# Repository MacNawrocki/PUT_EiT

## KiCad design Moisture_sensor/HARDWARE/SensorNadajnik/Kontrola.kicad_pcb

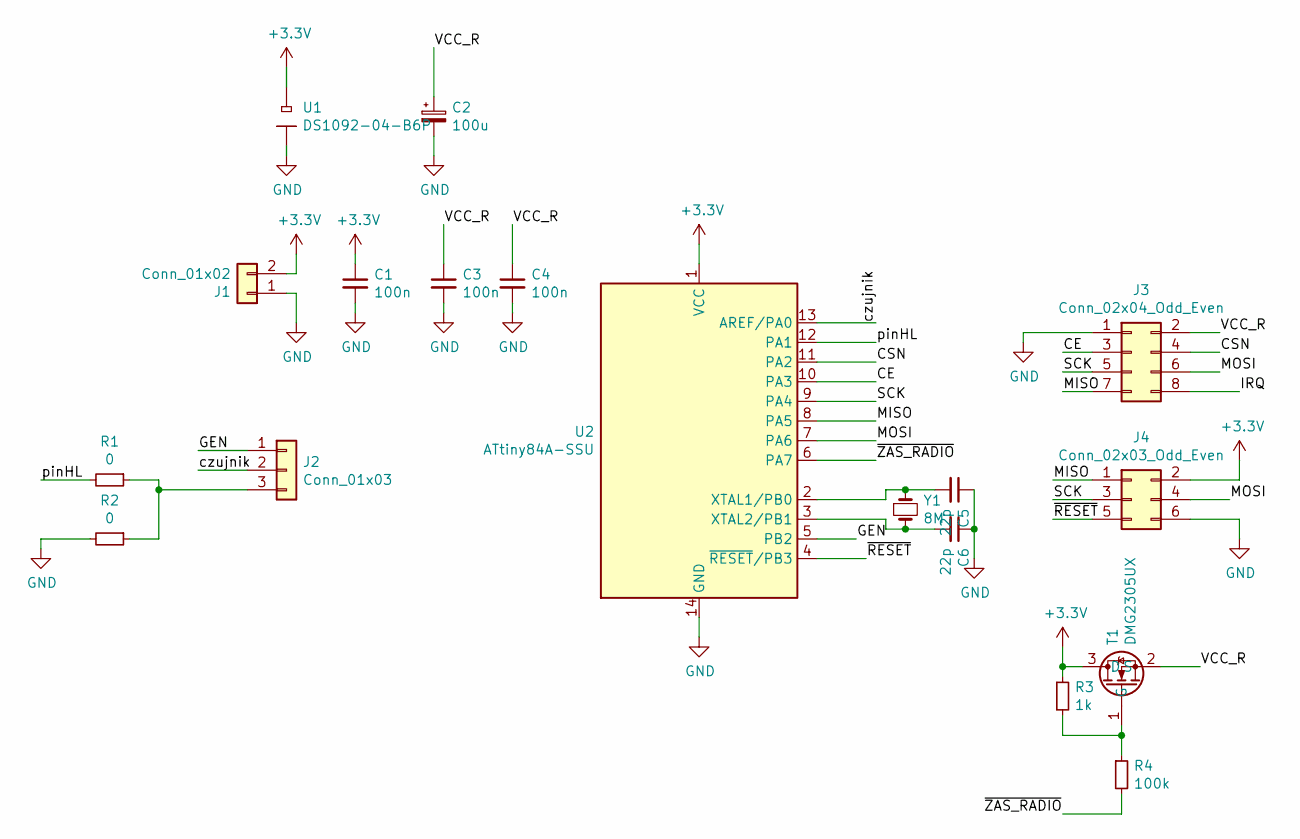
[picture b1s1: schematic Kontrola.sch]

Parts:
C1, C3, C4: 100n; C_0805_2012Metric_Pad1.15x1.40mm_HandSolder
C2: 100u; CP_EIA-3528-21_Kemet-B_Pad1.50x2.35mm_HandSolder
C5, C6: 22p; C_0805_2012Metric_Pad1.15x1.40mm_HandSolder
J1: Conn_01x02; PinHeader_1x02_P2.54mm_Vertical
J2: Conn_01x03; PinHeader_1x03_P2.54mm_Horizontal
J3: Conn_02x04_Odd_Even; PinHeader_2x04_P2.54mm_Vertical
J4: Conn_02x03_Odd_Even; PinHeader_2x03_P2.54mm_Vertical
R1, R2: 0; R_0805_2012Metric_Pad1.15x1.40mm_HandSolder
R3: 1k; R_0805_2012Metric_Pad1.15x1.40mm_HandSolder
R4: 100k; R_0805_2012Metric_Pad1.15x1.40mm_HandSolder
T1: DMG2305UX; SOT23_NASZE
U1: DS1092-04-B6P
U2: ATtiny84A-SSU; SOIC-14_3.9x8.7mm_P1.27mm
Y1: 8M; Crystal_HC49-4H_Vertical

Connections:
+3V3: C1.1, J1.2, J4.2, R3.1, T1.3 (D), U1.2 (-), U2.1 (VCC)
/CE: J3.3, U2.10 (PA3)
/CSN: J3.4, U2.11 (PA2)
/GEN: J2.1, U2.5 (PB2)
/IRQ: J3.8
/MISO: J3.7, J4.1, U2.8 (PA5)
/MOSI: J3.6, J4.4, U2.7 (PA6)
/SCK: J3.5, J4.3, U2.9 (PA4)
/VCC_R: C2.1, C3.1, C4.1, J3.2, T1.2 (S)
/czujnik: J2.2, U2.13 (AREF/PA0)
/pinHL: R1.2, U2.12 (PA1)
/~RESET: J4.5, U2.4 (~RESET~/PB3)
/~ZAS_RADIO: R4.2, U2.6 (PA7)
GND: C1.2, C2.2, C3.2, C4.2, C5.1, C6.1, J1.1, J3.1, J4.6, R2.2, U1.1 (+), U2.14 (GND)
unnamed: C5.2, U2.2 (XTAL1/PB0), Y1.1
unnamed: C6.2, U2.3 (XTAL2/PB1), Y1.2
unnamed: J2.3, R1.1, R2.1
unnamed: R3.2, R4.1, T1.1 (G)

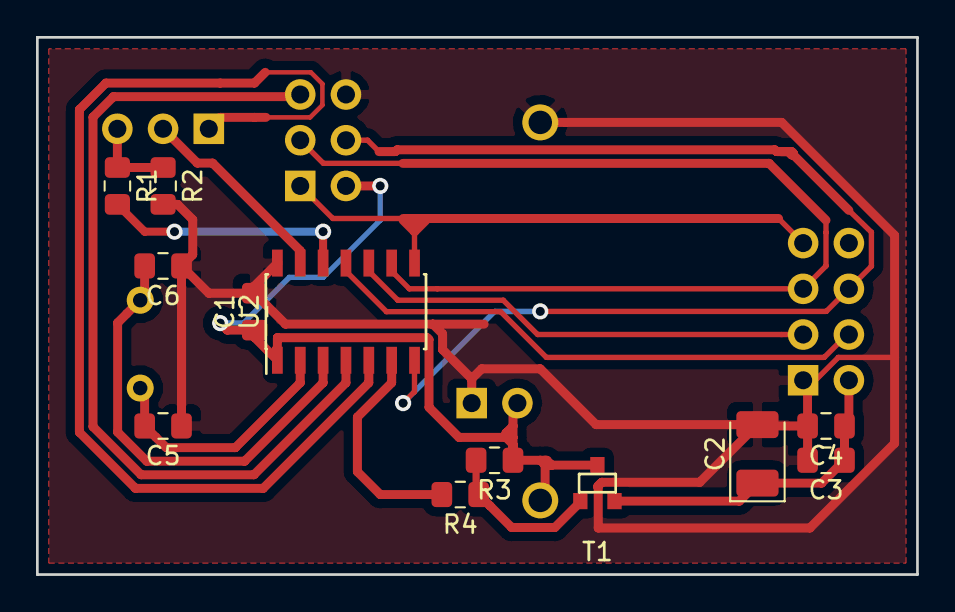
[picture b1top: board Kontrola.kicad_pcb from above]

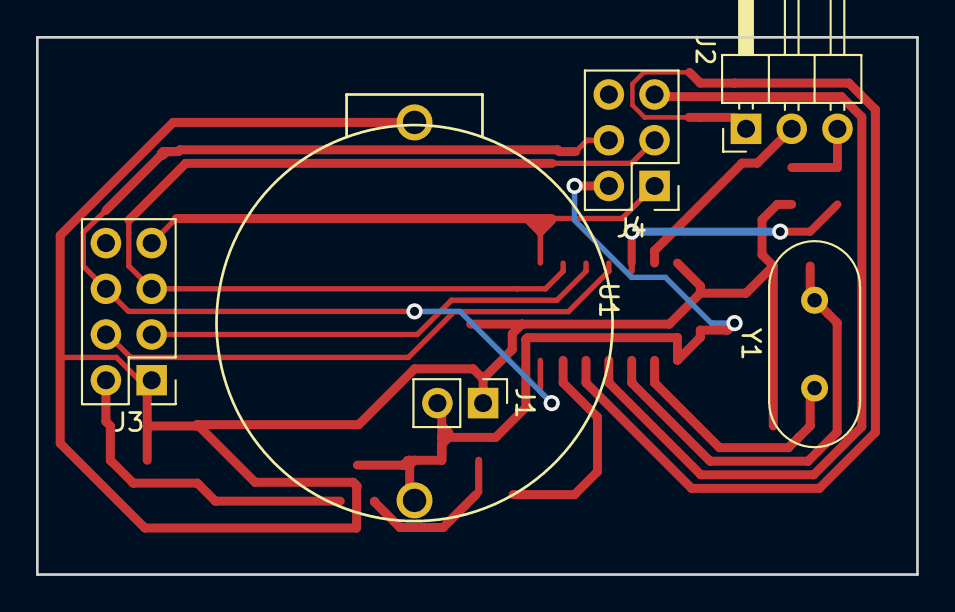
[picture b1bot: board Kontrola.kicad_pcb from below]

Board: 2 copper layers, 48.9 x 29.8 mm, 18 parts (6 on the bottom side), 17 nets.

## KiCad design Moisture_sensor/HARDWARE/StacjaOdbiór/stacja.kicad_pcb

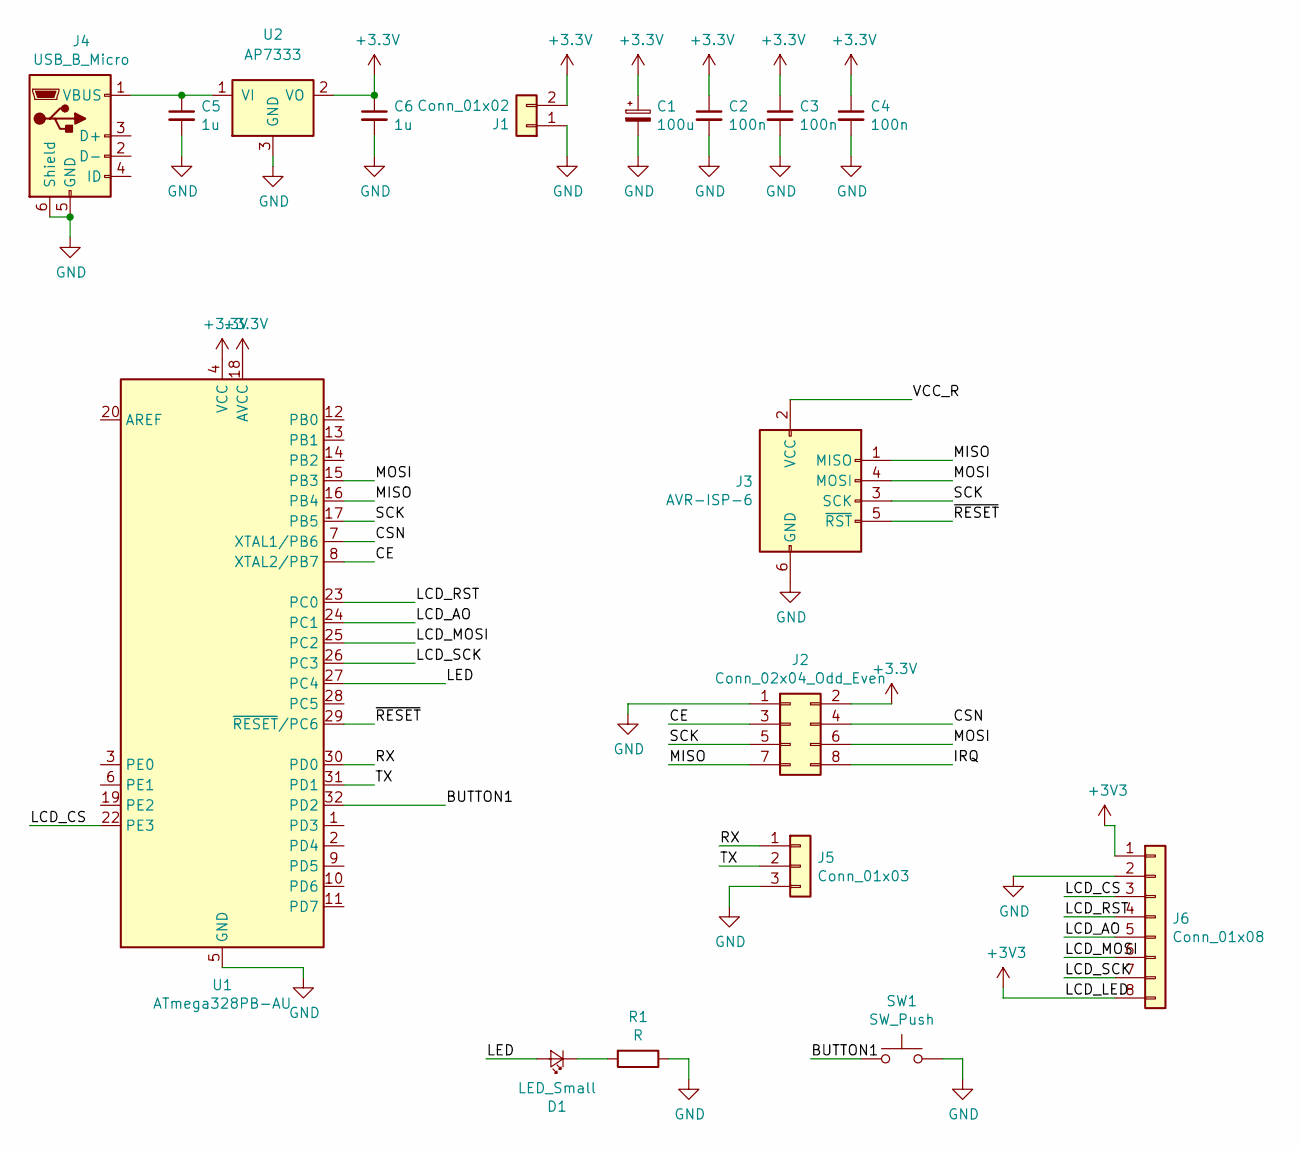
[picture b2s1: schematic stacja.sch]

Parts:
C1: 100u; CP_EIA-3528-21_Kemet-B_Pad1.50x2.35mm_HandSolder
C2, C3, C4: 100n; C_0805_2012Metric_Pad1.15x1.40mm_HandSolder
C5, C6: 1u; C_0805_2012Metric_Pad1.15x1.40mm_HandSolder
D1: LED_Small; LED_0805_2012Metric_Pad1.15x1.40mm_HandSolder
J1: Conn_01x02; PinHeader_1x02_P2.54mm_Vertical
J2: Conn_02x04_Odd_Even; PinHeader_2x04_P2.54mm_Vertical
J3: AVR-ISP-6; PinHeader_2x03_P2.54mm_Vertical
J4: USB_B_Micro; microusb
J5: Conn_01x03; PinHeader_1x03_P2.54mm_Vertical
J6: Conn_01x08; PinHeader_1x08_P2.54mm_Vertical
R1: R; R_0805_2012Metric_Pad1.15x1.40mm_HandSolder
SW1: SW_Push; BUTTON
U1: ATmega328PB-AU; TQFP-32_7x7mm_P0.8mm
U2: AP7333; SOT-23

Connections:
/BUTTON1: SW1.1, U1.32 (PD2)
/CE: J2.3, U1.8 (XTAL2/PB7)
/CSN: J2.4, U1.7 (XTAL1/PB6)
/IRQ: J2.8
/LCD_AO: J6.5, U1.24 (PC1)
/LCD_CS: J6.3, U1.22 (PE3)
/LCD_MOSI: J6.6, U1.25 (PC2)
/LCD_RST: J6.4, U1.23 (PC0)
/LCD_SCK: J6.7, U1.26 (PC3)
/LED: D1.2 (A), U1.27 (PC4)
/MISO: J2.7, J3.1 (MISO), U1.16 (PB4)
/MOSI: J2.6, J3.4 (MOSI), U1.15 (PB3)
/RX: J5.1, U1.30 (PD0)
/SCK: J2.5, J3.3 (SCK), U1.17 (PB5)
/TX: J5.2, U1.31 (PD1)
/VCC_R: J3.2 (VCC)
/~RESET: J3.5 (~RST), U1.29 (~RESET~/PC6)
GND: C1.2, C2.2, C3.2, C4.2, C5.2, C6.2, J1.1, J2.1, J3.6 (GND), J4.5 (GND), J4.6 (Shield), J5.3, J6.2, R1.1, SW1.2, U1.5 (GND), U1.21 (GND), U2.3 (GND)
unnamed: C5.1, J4.1 (VBUS), U2.1 (VI)
unnamed: D1.1 (K), R1.2

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
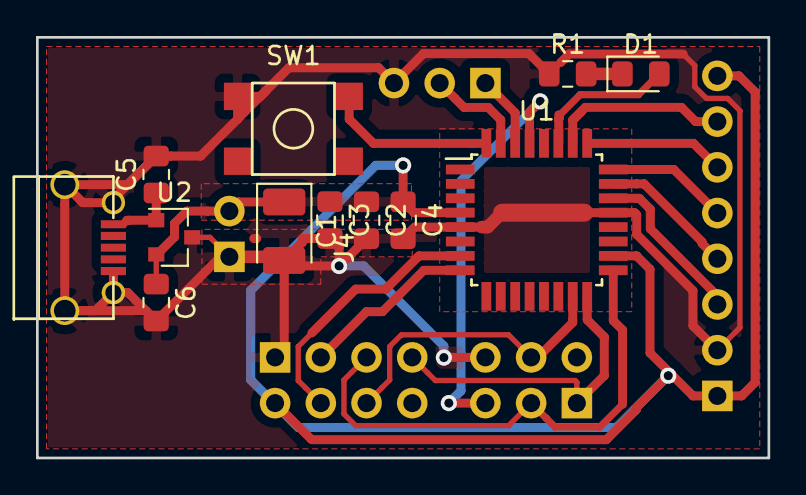
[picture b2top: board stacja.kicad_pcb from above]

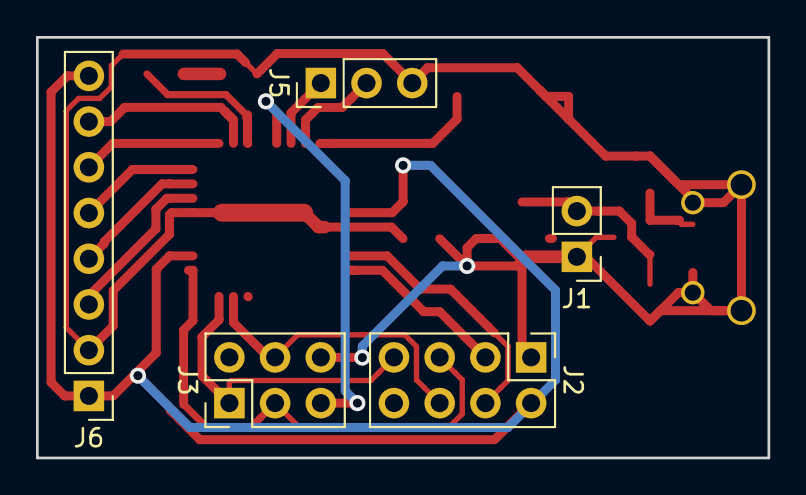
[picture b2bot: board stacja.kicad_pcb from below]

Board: 2 copper layers, 40.6 x 23.4 mm, 17 parts (5 on the bottom side), 19 nets.

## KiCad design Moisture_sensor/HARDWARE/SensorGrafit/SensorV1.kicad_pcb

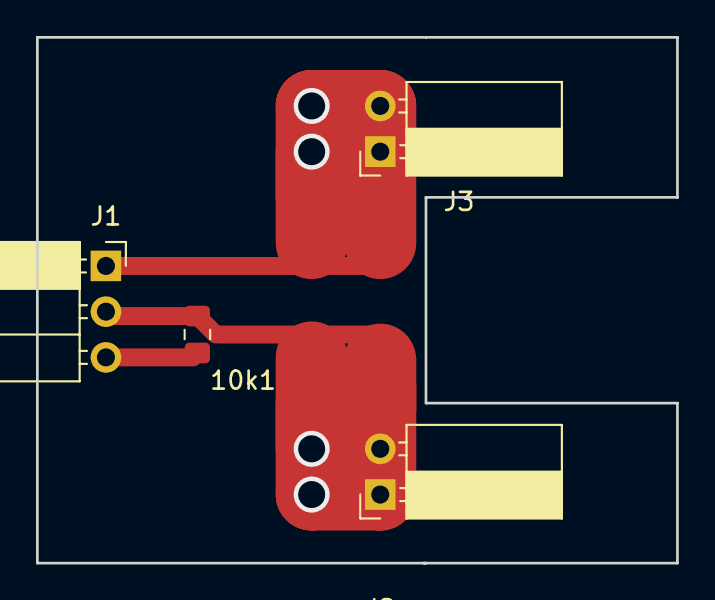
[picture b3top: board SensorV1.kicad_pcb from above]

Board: 2 copper layers, 35.6 x 29.2 mm, 4 parts (0 on the bottom side), 3 nets.

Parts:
10k1: R_Small; R_0805_2012Metric_Pad1.15x1.40mm_HandSolder
J1: Conn_01x03; PinSocket_1x03_P2.54mm_Horizontal
J2, J3: Conn_01x02; PinSocket_1x02_P2.54mm_Horizontal

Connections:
unnamed: 10k1.1, J1.2, J2.1, J2.2
unnamed: 10k1.2, J1.3
unnamed: J1.1, J3.1, J3.2

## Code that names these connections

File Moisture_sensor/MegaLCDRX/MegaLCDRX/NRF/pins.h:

#ifndef PINS_H_
#define PINS_H_

/*
Connection:
ATMega328PB	PIN	To
PB3	to	MOSI		programator/radio
PB4	to	MISO		programator/radio
PB5	to	SCK			programator/radio
PB6	to	CSN			radio
PB7	to	CE			radio
PC0	to	LCD_RST		wywietlacz
PC1	to	LCD_AO		wywietlacz
PC2	to	LCD_MOSI	wywietlacz
PC3	to	LCD_SCK		wywietlacz
PC4	to	LED			dioda na p³ytce
PC6	to	RESET		programator/radio
PD0	to	RX
PD1	to	TX
PD2	to	BUTTON1		guzik na p³ytce
PE3	to	LCD_CS		wywietlacz
*/ 

#define BIT(x)				1<<(x)
#define SET_BIT(x, y)		(x) |= (BIT(y))
#define CLEAR_BIT(x, y)		(x) &= (~(BIT(y)))
#define SET_OUTPUT(pin)		(pin ## _DDR)|=_BV(pin)
#define SET_INPUT(pin)		CLEAR_BIT((pin ## _DDR),(pin))
#define SET_HIGH(pin)		(pin ## _PORT)|=_BV(pin)
#define SET_LOW(pin)		(pin ## _PORT)&=!_BV(pin)

#define MOSI PB3
#define MOSI_DDR DDRB
#define MOSI_PORT PORTB

#define MISO PB4
#define MISO_DDR DDRB
#define MISO_PORT PORTB
#define MISO_PIN  PINB


#define SCK PB5
#define SCK_DDR DDRB
#define SCK_PORT PORTB

#define CSN PB6
#define CSN_DDR DDRB
#define CSN_PORT PORTB

#define CE PB7
#define CE_DDR DDRB
#define CE_PORT PORTB

#define LCD_RST PC0
#define LCD_RST_DDR DDRC
#define LCD_RST_PORT PORTC

#define LCD_AO PC1
#define LCD_AO_DDR DDRC
#define LCD_AO_PORT PORTC

#define LCD_MOSI PC2
#define LCD_MOSI_DDR DDRC
#define LCD_MOSI_PORT PORTC

#define LCD_SCK PC3
#define LCD_SCK_DDR DDRC
#define LCD_SCK_PORT PORTC

#define LED PC4
#define LED_DDR DDRC
#define LED_PORT PORTC

#define BUTTON PD2
#define BUTTON_DDR DDRD
#define BUTTON_PORT PORTD

#define LCD_CSS PE3
#define LCD_CSS_DDR DDRE
#define LCD_CSS_PORT PORTE

#endif /* PINS_H_ */

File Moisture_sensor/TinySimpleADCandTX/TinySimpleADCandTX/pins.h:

#ifndef PINS_H_
#define PINS_H_

/*
Connection:
ATTiny84 PIN To 
1         To +3.3V
2  [PB0]  To XTAL1      (kwarc-nieu¿ywany)
3  [PB1]  To XTAL2      (kwarc-nieu¿ywany)
4  [PB3]  To RESET      (USBasp)
5  [PB2]  To GEN        (czujnik)
6  [PA7]  To ZAS_RADIO  (nRF24L01)
7  [PA6]  To MOSI       (nRF24L01)&(USBasp)
8  [PA5]  To MISO       (nRF24L01)&(USBasp)
9  [PA4]  To SCK        (nRF24L01)&(USBasp)
10 [PA3]  To CE	        (nRF24L01)
11 [PA2]  To CSN        (nRF24L01)
12 [PA1]  To pinHL      (czujnik)
13 [PA0]  To czujnik    (czujnik)
14        To GND
 */ 

#define BIT(x)				1<<(x)
#define SET_BIT(x, y)		(x) |= (BIT(y))
#define CLEAR_BIT(x, y)		(x) &= (~(BIT(y)))
#define SET_OUTPUT(pin)		(pin ## _DDR)|=_BV(pin)
#define SET_INPUT(pin)		CLEAR_BIT((pin ## _DDR),(pin))
#define SET_HIGH(pin)		(pin ## _PORT)|=_BV(pin)
#define SET_LOW(pin)		(pin ## _PORT)&=!_BV(pin)
#define IS_LOW(pin)			!((pin ## _PIN) & _BV(pin))
#define IS_HIGH(pin)		((pin ## _PIN) & _BV(pin))

//Generator - obecnie dioda LED
#define GEN PB2
#define GEN_DDR	DDRB
#define GEN_PORT PORTB
//Zasilanie radia - bramka MOSFETa
#define ZASRAD PA7
#define ZASRAD_DDR DDRA
#define ZASRAD_PORT PORTA
//MOSI
#define MOSI PA6
#define MOSI_DDR DDRA
#define MOSI_PORT PORTA
//MISO
#define MISO PA5
#define MISO_DDR DDRA
#define MISO_PORT PORTA
#define MISO_PIN PINA
//SCK
#define SCK PA4
#define SCK_DDR DDRA
#define SCK_PORT PORTA
//CE
#define CE PA3
#define CE_DDR DDRA
#define CE_PORT PORTA
//CSN
#define CSN PA2
#define CSN_DDR DDRA
#define CSN_PORT PORTA
//Czujnik
#define CZUJ PA0
#define CZUJ_DDR DDRA
#define CZUJ_PORT PORTA
#define CZUJ_PCINT PCINT0 
#define CZUJ_PIN PINA


//Generator - obecnie dioda LED
#define PINHL PA1
#define PINHL_DDR	DDRA
#define PINHL_PORT PORTA

#endif /* PINS_H_ */
